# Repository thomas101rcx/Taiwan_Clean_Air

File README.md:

# Taiwan_Clean_Air
pilot project for air quality monitoring in Taiwan

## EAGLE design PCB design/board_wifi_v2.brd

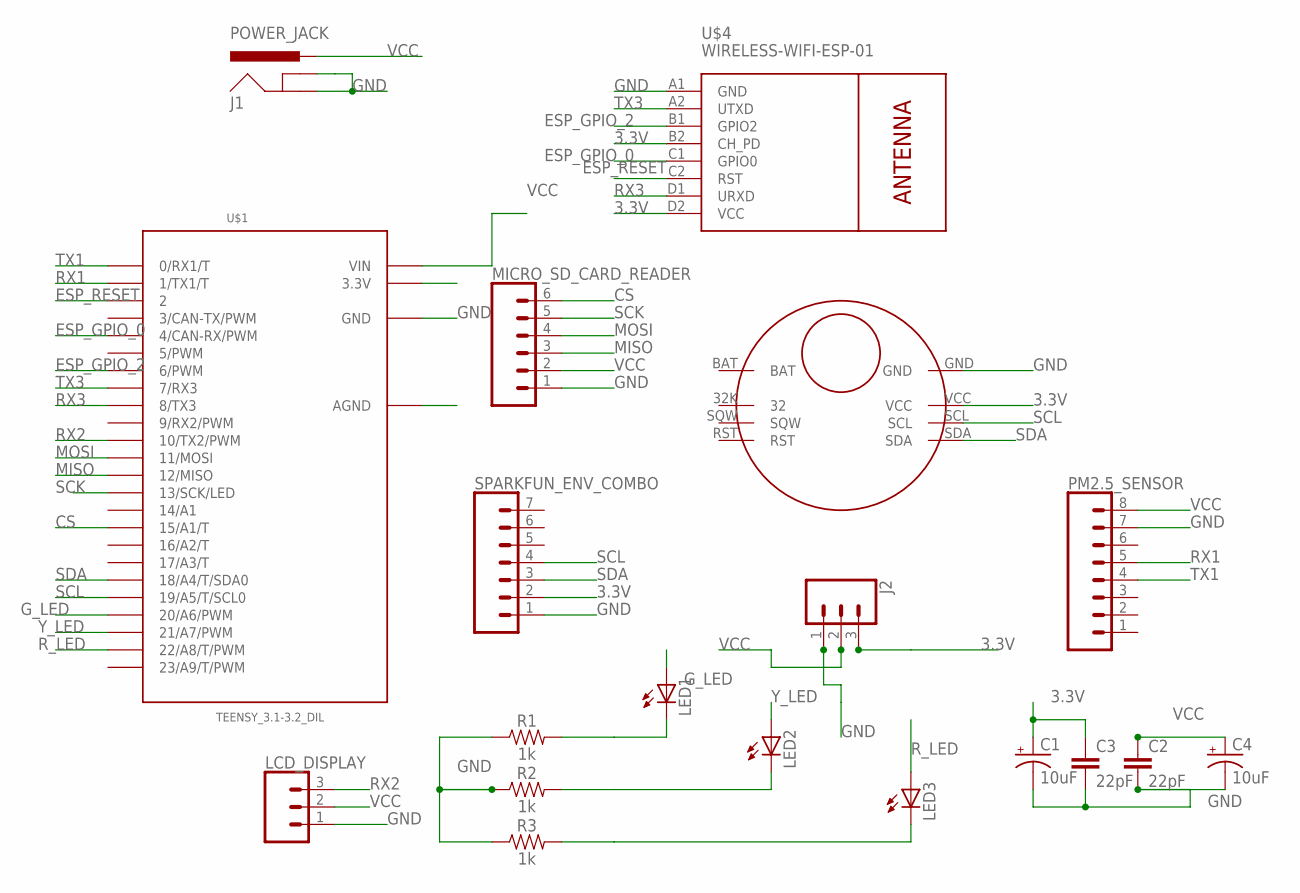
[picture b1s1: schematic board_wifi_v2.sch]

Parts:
C1, C4: 10uF; CPOL-RADIAL-2.5MM-5MM
C2, C3: 22pF; CAP-PTH-2.54
J1: POWER_JACK; POWER_JACK_PTH
J2: CONN_03LONGPADS; 1X03_LONGPADS
LCD_DISPLAY: CONN_031X03_NO_SILK; 1X03_NO_SILK
LED1, LED2, LED3: LED3MM
MICRO_SD_CARD_READER: CONN_06LONGPADS; 1X06_LONGPADS
PM2.5_SENSOR: CONN_08NO_SILK_FEMALE_PTH; 1X08_NO_SILK
R1, R2, R3: 1k; AXIAL-0.3
SPARKFUN_ENV_COMBO: CONN_07NO_SILK; 1X07_NO_SILK
U$1: TEENSY_3.1-3.2_DIL; TEENSY_3.0-3.2&LC_DIL
U$2: RTCCLOCK
U$4: WIRELESS-WIFI-ESP-01

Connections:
3.3V: C1.1 (+), C3.1, J2.3, SPARKFUN_ENV_COMBO.2, U$2.VCC, U$4.B2 (CH_PD), U$4.D2 (VCC)
CS: MICRO_SD_CARD_READER.6, U$1.15/A1 (15/A1/T)
ESP_GPIO_0: U$1.4 (4/CAN-RX/PWM), U$4.C1 (GPIO0)
ESP_GPIO_2: U$1.6 (6/PWM), U$4.B1 (GPIO2)
ESP_RESET: U$1.2, U$4.C2 (RST)
GND: C1.2 (-), C2.2, C3.2, C4.2 (-), J1.GND, J1.GNDBREAK, J2.1, LCD_DISPLAY.1, MICRO_SD_CARD_READER.1, PM2.5_SENSOR.7, R1.P$1 (1), R2.P$1 (1), R3.P$1 (1), SPARKFUN_ENV_COMBO.1, U$1.GND, U$2.GND, U$4.A1 (GND)
G_LED: LED1.A, U$1.20/A6 (20/A6/PWM)
MISO: MICRO_SD_CARD_READER.3, U$1.12 (12/MISO)
MOSI: MICRO_SD_CARD_READER.4, U$1.11 (11/MOSI)
unnamed: LED1.K (C), R1.P$2 (2)
unnamed: LED2.K (C), R2.P$2 (2)
unnamed: LED3.K (C), R3.P$2 (2)
RX1: PM2.5_SENSOR.5, U$1.1 (1/TX1/T)
RX2: LCD_DISPLAY.3, U$1.10 (10/TX2/PWM)
RX3: U$1.8 (8/TX3), U$4.D1 (URXD)
R_LED: LED3.A, U$1.22/A8 (22/A8/T/PWM)
SCK: MICRO_SD_CARD_READER.5, U$1.13 (13/SCK/LED)
SCL: SPARKFUN_ENV_COMBO.4, U$1.19/A5 (19/A5/T/SCL0), U$2.SCL
SDA: SPARKFUN_ENV_COMBO.3, U$1.18/A4 (18/A4/T/SDA0), U$2.SDA
TX1: PM2.5_SENSOR.4, U$1.0 (0/RX1/T)
TX3: U$1.7 (7/RX3), U$4.A2 (UTXD)
VCC: C2.1, C4.1 (+), J1.PWR, J2.2, LCD_DISPLAY.2, MICRO_SD_CARD_READER.2, PM2.5_SENSOR.8, U$1.VIN
Y_LED: LED2.A, U$1.21/A7 (21/A7/PWM)

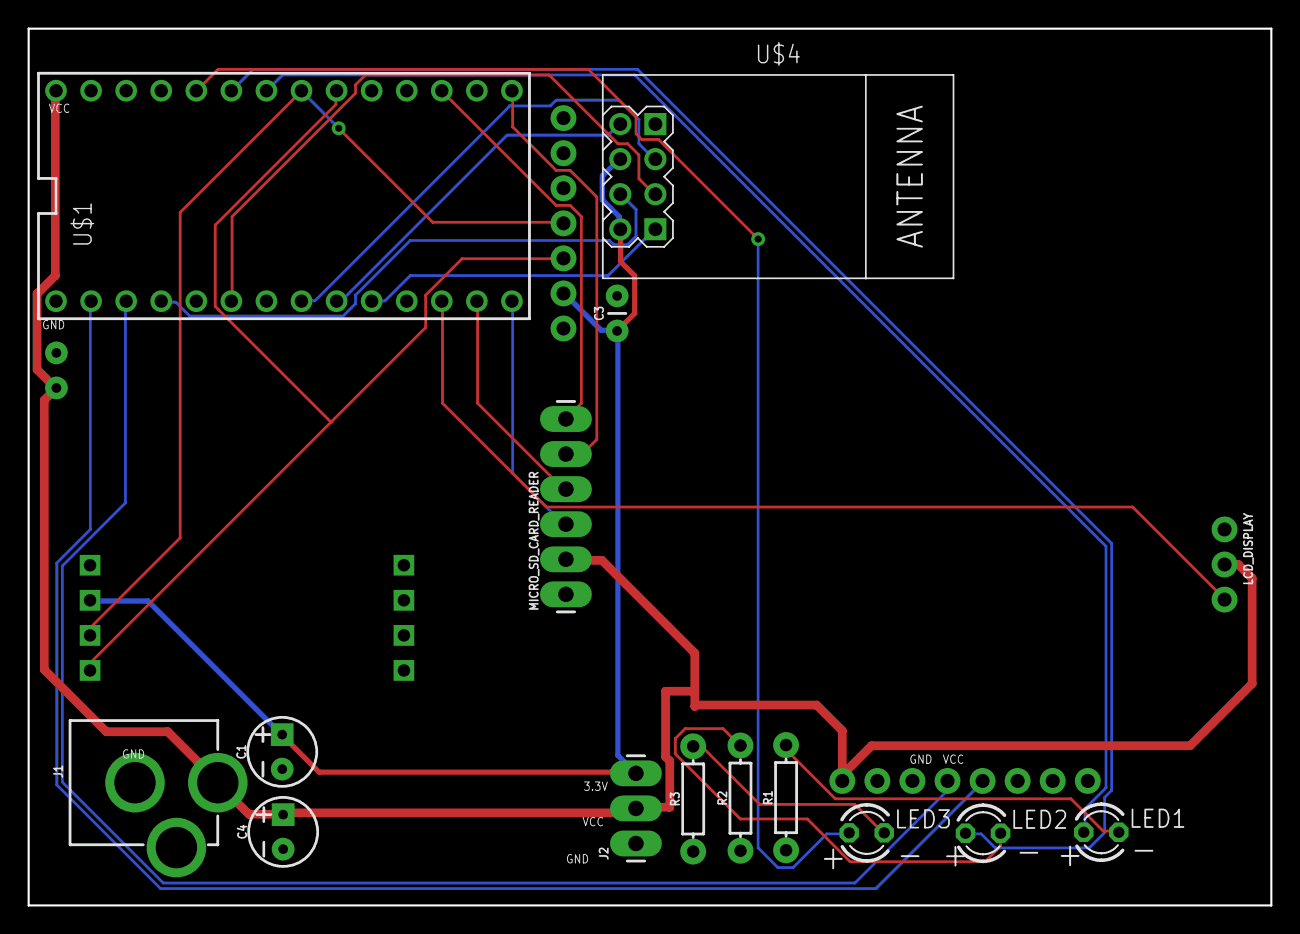
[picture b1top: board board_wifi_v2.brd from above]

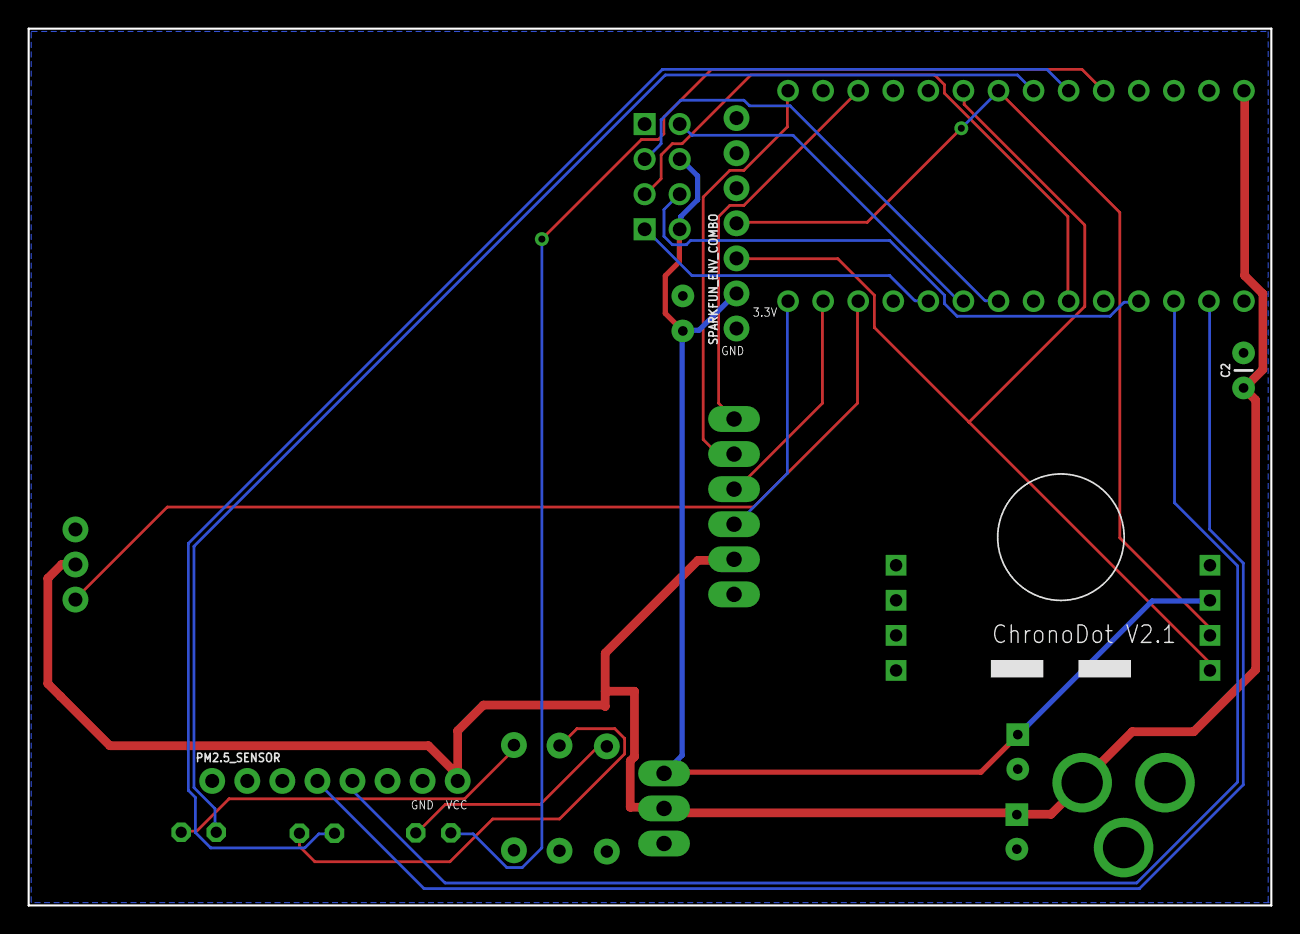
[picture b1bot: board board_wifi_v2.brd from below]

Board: 2 copper layers, 90.0 x 63.5 mm, 19 parts (4 on the bottom side), 23 nets.

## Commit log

2018-08-21 08212018Commit
2018-08-21 08212018Commit2
2018-08-21 08212018Commit3
2018-10-14 10142018Commit

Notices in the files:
parts and their libraries:
SparkFun-Capacitors: Licensing: Creative Commons ShareAlike 4.0 International - https://creativecommons.org/licenses/by-sa/4.0
diy-modules: Released under the Creative Commons Attribution 4.0 International License: http://creativecommons.org/licenses/by/4.0
